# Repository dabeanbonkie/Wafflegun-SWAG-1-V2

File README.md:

# Wafflegun-SWAG-1

# Description
The S.W.A.G (Stroop-Wafel-Assault-Gun) is the latest generation of food based arms. It is a tire driven stroopwafel launcher with an auto loading system. It uses two motors for the launch and a servo for the loader and runs on a Xiao RP2040. The wafflegun can be used to hand out stroopwafels to an entire group from a distance within the span of just a couple seconds.

# Assembly
TO assemble the S.W.A.G start off by ordering the pcb from any shop you prefer, although i will explain how i ordered it using JLCPCB. Log in to JLCPCB and the hit "Order Now". From there you will be asked to add the gerber ZIP file from the repo. This will give you everything you need and the board should load on the site. Dont change anything for the rest of the order process, just hit next after you've added the gerber files zip. Following this pay for your pcb and then you're all done with the pcb until its delivered to you.

It should look like this is JLCPCB:

Note: I will be refering to the side of the pcb with the letters as the top and from there i call the other sides left, right and bottom. This is also diferent from the side of the pcb as in the working layer.

When the pcb arrives grab a BD139 NPN-transistor and place it in the holes near the left side if the pcb with the white part facing towards the inside of the pcb (pictued in example 1). Then Solder the legs of the transistor to the pcb from the bottom side while making sure no bridges are made (pictured in example 2). Then cut off the legs until the point they are soldered at (pictured in example 3)

Example 1:

Example 2:

Example 3:

Next grab all your curved pin headers, I used male dupont surved pin headers in my example because those were the ones i had, but i would recomend using female dupont curved pin headers. Both are fine so use whichever one you have but if you have to order them, order the female headers. You should have 3: 1 * 2 headers and 2: 1 * 3 headers. Put each of the pin headers in the hole that corresponds to the width (pictured in example 4). Then as with the transistor, solder each pin from the bottom side to the pcb (pictured in example 5).

Example 4:

Example 5:

Now here comes the hard part, were using a tiny 1.5K ohm SMD-0402 resistor. For the next two solders we will be using solder paste as its really the only way to get a solder this precise. I would also recomend using a magnfying glass at this point as this resistor is very small. Place two small bits of solder paste on the two pads on which we will solder the resistor (pictured in example 6). Then incredibly gently place the resistor on the two pads with the resistors black side facing up and use a heat gun to carefully melt the solder while making sure not to stay in one place too long as not to melt the pcb. The final result should look like example 7.

Example 6:

Example 7:

Lastly grab your solder paste again, and place a small glob on each of the solder pads for XIAO RP2040 (pictured in example 8). Then carefully place the XIAO RP2040 on top of the pads making sure each connection lines up with the micro-usb port facing towards the right side of the pcb (pictured in example 9). Then gently move the heatgun over the pcb to melt the solder while making sure not to melt the pcb or any other nearby components. The final result should look like example 9.

Example 8:

ELFR1021
Example 9:

You are now done with making the PCB for S.W.A.G-1

Kicad wiring schematic of the pcb:

Kicad wiring schematic of the full circuit:

To build the rest of the cuircuit start by grabbing your ELFR1021 DC high speed motors and cutting off the connector that is attached. After this crimp a dupont header on each wire of both of the motors. If you have used Female headers on the pcb, use male headers on the motors. If you have used male headers (like me) on the pcb use female headers on the motors. 

It should look like this:

After this attach red wire of both motors to the pinheaders group 5 on the pcb, and the black wires to the pinheader group 3 on the pcb.

It should look like this:

Next take your SG90 servo and attach it to pinheader group 2 on the pcb with the brown wire of the servo (GND wire) being attached to the right-sided pin on pinheader group 2. If the brown wire is on the right pin, the red and yellow wire are too.

It should look like this:

Following this i dont have a good physical example for the buttons. In the wiring diagram i show a SW-SP3T three way switch where one position is floating so no signal goes through the buttons meaning no part is turned on, and the other two positions going to either the motor or the servo so you can toggle the motor and servo separately. I do not have an SW_SP3T available due to a shipping error so the best i can do is show how to connect it. 

-First connect the right pin on pin header group 4 to the COM Pin ( also knows as the common pin and pin 3 on the wiring diagram showed earlier.). The brown wire is the wire you would connect to the common pin of the SW_SP3T.

-Then connect output 1 on the SW-SP3T to the middle pin on pinheader group 4 on the pcb and connect output 2 on the SW-SP3T to the left pin on pinheader group 4 on the pcb.

-Ouput 3 will be left floating as that will be the "off" pin so it has no output.

If you do all of this you can switch between turning on the servo, turning on the motor & having both off.

Next up take your 4*AA battery holder and if necessary crimp on female dupont headers to both wires if you have male headers on your pcb and male headers to both wires if you have female headers on your pcb.

It should look like this:

Then attach the red wire to specifically the right-sided pin on pin header ground 1 on the pcb, and the black wire to the lift sided pin  on pin header ground 1 on the pcb.

It should look like this:

With this all the wiring is done! Now on to the 3D-printed parts.

Start by printing all of the pieces in the STL files folder. The gear pieces need to be printed twice but all of the other pieces need to be printed only once.

Start by grabbing both "gear and wheel support" pieces and add 7 bearings with a 6mm inner diameter and a 13mm outer diameter to each support. Make sure to leave one hole on the far side with the extention empty as that one wont hold a gear.

It should look like this:

After that start adding your gears. Start by adding gear 1 to the first bearing from the side with the extention. Make sure to add the bearing to the flat side of the support, otherwise it will not fit.

After this add gear 2 to the bearing beside gear 1:

Then add gear 3 beside gear 2:

Then add gear 4 beside gear 3:

Then add gear 5 beside gear 4:

Then add gear A beside gear 5:

Then add gear B beside gear A:

Now repeat this exactly on the other support.

Next up, use Plastic glue to glue together barrel 1 and barrel 2. You can use glue here as these pieces never need to be seperated and are only seperate for easy of printing.

It should look roughly like this:

After this glue on the two gear and wheel support pieces making it so the side with the extention on the supports is on the wide side of the barrel with the lip. If that doesnt make sense i understand so ill show two angles of this step:

Next grab Support piece 2 with the stock attached, and slide it through the bottom square hole of the barrel. No glue required as this part might need to be seperated for maintenence. For this step i will also add 2 angles:

Then grab Support piece 1 and do the same as with support piece 2, exept this time on the top square hole and without the stock.

Following this add the PCB and Battery holder to the back of the barrel, glue is optional, you could add it if it falls off but if placed right it should fit nice and snug. For this i will again add two angles for clarity:

The next step is adding the actual electronics. First take the pcb and add it to the pcb holder (i left my battery unconnected cause its more dificult to add the pcb to the holder with the battery attached):

it should look like this:

Next add the battery on top of the pcb holder. 

After this add the motors under the extention on the gear and wheel supports, it should be a snug fit. Also remember to make sure the connector from gear 1 and the connector on the motor line up

Do the same on the other gear and wheel support.

Now add the 65mm rubber wheels to the "gear B" gears on both supports. It should be a snug fit.

Then its time to add the shells. Grab shell 1 and 2 and attach them to the barrel with them also snugly fitting around the support pieces. I will add three angles cause this can be really tricky:

Next up its time for the waffle magazine piece, i recomend laying the wafflegun on its side for this portion as the glue will dry easier without it falling if its on its side. So start off by finding the hole that the magazine attaches to and putting some plastic glue on the edges before placing on the magazine making sure that the holes are alligned on both.

This is where the hole for the magazine is:

this is how to place it:

After this its time to add the servo holder. Keep the wafflegun on its side for this part. This part has to attach right next to the the magazine. Using plastic glue, glue this part to Shell-2 as that is where the part has the largest surface area of contact.

Next up place the servo inside the servo holder, i have no physical images for this so ill try to explain how to place it. Place the servo inside the holder while making sure the wires at the back of the servo are facing the hole next to the hole for the waffle magazine.

This is the hole to put all the wires for the servo through:

Then take the wires and push them through the barrel towards the pcb, where you can connect it to the coresponding pins. The Arm of the servo should fit into the hole in the magazine itself

This is the hole the servo arm goes through:

The servo arm can then push stroopwafels into the barrel as another falls into place to replace the one thats been loaded, thus making the autoloading work.

The last piece of the puzzle is the waffle pusher, which pushes the stroopwafel to the drive tires that it gets shot from. To place it go to the side opposite of the waffle magazine  and push the long pusher piece into the hole with the tail of the piece leading to the grip and stock so you can push the waffles from where you hand is holding the S.W.A.G-1.

And now you are (finally) done with building S.W.A.G-1

# Onshape Link for the shell:

https://cad.onshape.com/documents/747ccfec51634792c2777cca/w/01fb49ed376507a91ea61a49/e/87ecc3b4d7d030e5be71dfa8

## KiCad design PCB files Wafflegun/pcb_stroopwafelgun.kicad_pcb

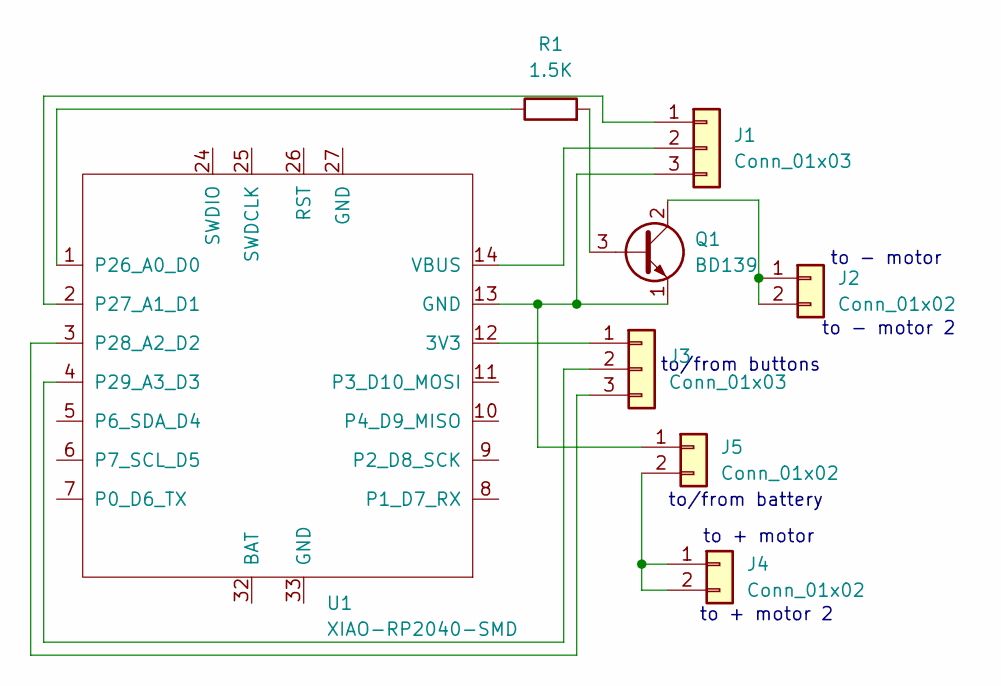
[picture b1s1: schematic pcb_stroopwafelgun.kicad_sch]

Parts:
J1, J3: Conn_01x03; PinSocket_1x03_P2.54mm_Horizontal
J2, J4, J5: Conn_01x02; PinSocket_1x02_P2.54mm_Horizontal
Q1: BD139; TO-126-3_Vertical
R1: 1.5K; R_0402_1005Metric
U1: XIAO-RP2040-SMD

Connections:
unnamed: J1.1, U1.2 (P27_A1_D1)
unnamed: J1.2, U1.14 (VBUS)
unnamed: J1.3, J5.1, Q1.1 (E), U1.13 (GND)
unnamed: J2.1, J2.2, Q1.2 (C)
unnamed: J3.1, U1.12 (3V3)
unnamed: J3.2, U1.4 (P29_A3_D3)
unnamed: J3.3, U1.3 (P28_A2_D2)
unnamed: J4.1, J4.2, J5.2
unnamed: Q1.3 (B), R1.2
unnamed: R1.1, U1.1 (P26_A0_D0)

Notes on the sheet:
to - motor
to + motor 2
to/from battery
to/from buttons
to - motor 2
to + motor

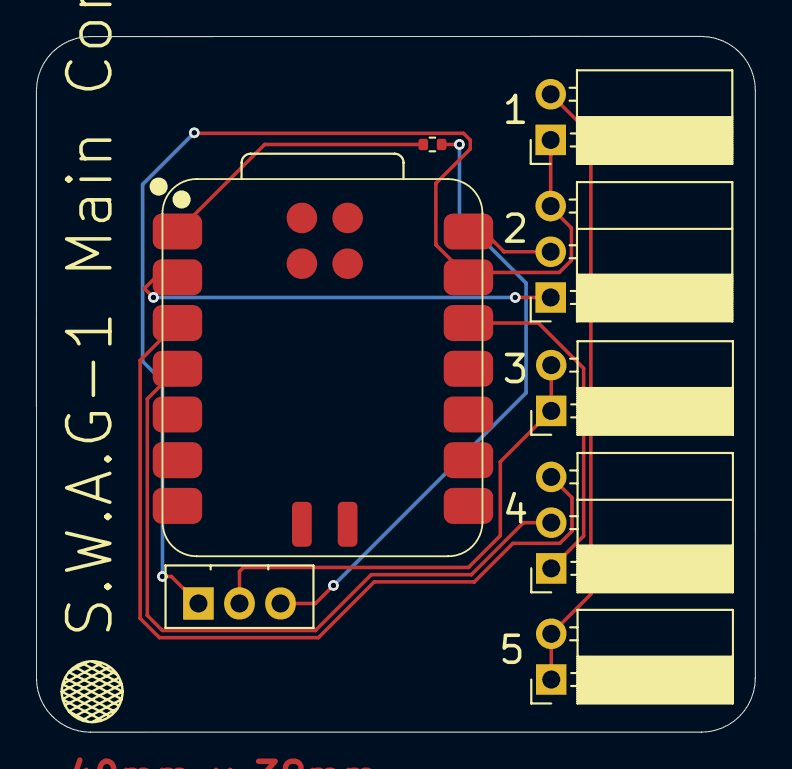
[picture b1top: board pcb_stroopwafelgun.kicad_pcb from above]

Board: 2 copper layers, 39.9 x 38.7 mm, 8 parts (0 on the bottom side), 10 nets.

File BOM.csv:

"Reference","Qty","Value","DNP","Exclude from BOM","Exclude from Board","Footprint","Datasheet"
"J1,J3","2","Conn_01x03","","","","Connector_PinSocket_2.54mm:PinSocket_1x03_P2.54mm_Horizontal",""
"J2,J4,J5","3","Conn_01x02","","","","Connector_PinSocket_2.54mm:PinSocket_1x02_P2.54mm_Horizontal",""
"Q1","1","BD139","","","","Package_TO_SOT_THT:TO-126-3_Vertical","http://www.st.com/internet/com/TECHNICAL_RESOURCES/TECHNICAL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"
"R1","1","1.5K","","","","Resistor_SMD:R_0402_1005Metric",""
"U1","1","XIAO-RP2040-SMD","","","","seeed:XIAO-RP2040-SMD",""

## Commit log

2026-06-27 Rename gear 2 WAFFLEGUN (1).stl to gear 3 WAFFLEGUN.stl
2026-06-27 Add files via upload
    COMMIT
2026-06-27 Rename Gear 1 WAFFLEGUN.stl to gear 1 WAFFLEGUN.stl
2026-06-27 Rename S.W.A.G-1 Wafflegun - PCB & Battery holder (1).stl to S.W.A.G-1 Wafflegun - PCB & Battery holder.stl
